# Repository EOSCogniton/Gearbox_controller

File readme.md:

# Gearbox controller

* Shield pour Arduino Uno
* Pour le shifter d'OPTIMUS v1.0

## Utilité :
* Convertis les signaux 12V du moteur en 5V pour l'arduino
* Convertis les signaux 5V de l'arduino en 12V pour le moteur
* Permet de se connecter avec des connecteurs molex KK à l'arduino
* Inclus un circuit de protection pour l'alimentation de l'arduino

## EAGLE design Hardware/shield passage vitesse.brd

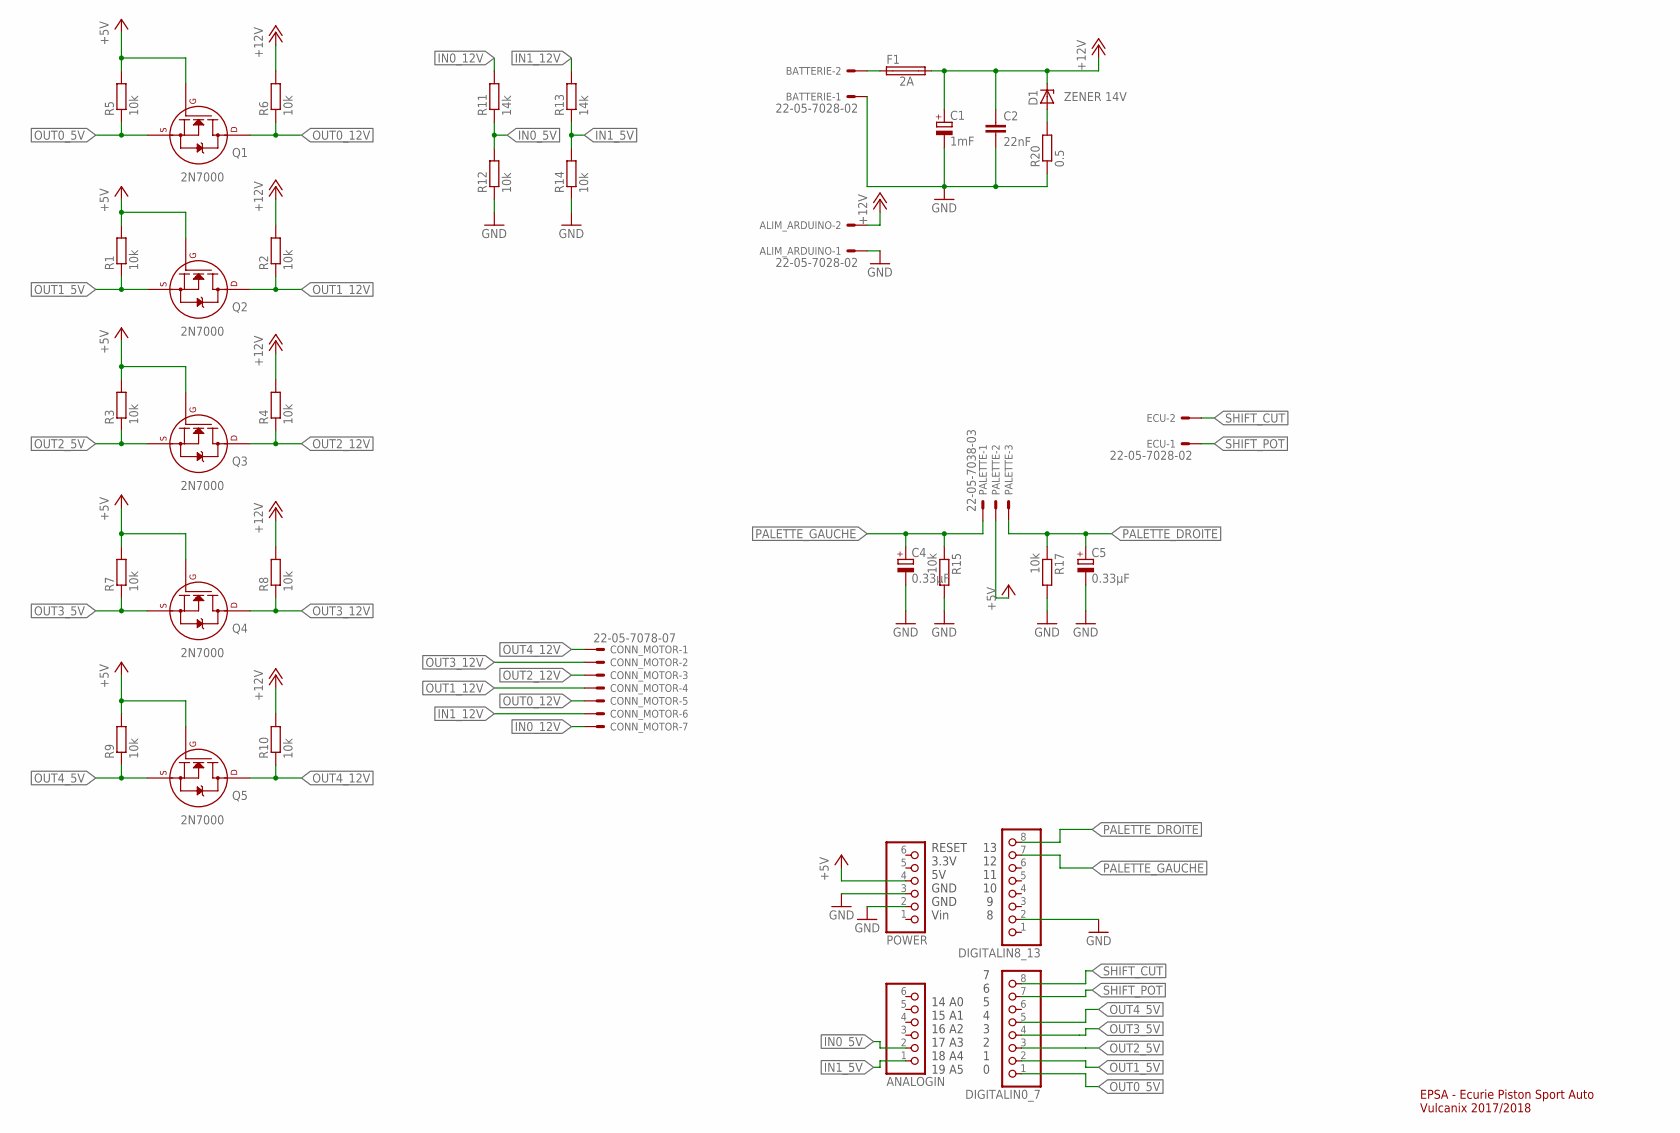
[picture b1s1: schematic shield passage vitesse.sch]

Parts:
ALIM_ARDUINO: 22-05-7028-02; 7395-02
ANALOGIN: PINHD-1X6CB; 1X06-CLEANBIG
BATTERIE: 22-05-7028-02; 7395-02
C1: 1mF; E7,5-16
C2: 22nF; C025-025X050
C4, C5: 0.33µF; E2,5-6E
CONN_MOTOR: 22-05-7078-07; 7395-07
D1: ZENER 14V; DO41Z10
DIGITALIN0_7, DIGITALIN8_13: PINHD-1X8CLEANBIG; 1X08-CLEANBIG
ECU: 22-05-7028-02; 7395-02
F1: 2A; SH25
PALETTE: 22-05-7038-03; 7395-03
POWER: PINHD-1X6CB; 1X06-CLEANBIG
Q1, Q2, Q3, Q4, Q5: 2N7000; TO-92
R1, R2, R3, R4, R5, R6, R7, R8, R9, R10, R12, R14, R15, R17: 10k; 0204/7
R11, R13: 14k; 0204/7
R20: 0.5; 0309/12

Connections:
+5V: PALETTE.2, POWER.4, Q1.2 (G), Q2.2 (G), Q3.2 (G), Q4.2 (G), Q5.2 (G), R1.2, R3.2, R5.2, R7.2, R9.2
+12V: ALIM_ARDUINO.2, C1.+, C2.1, D1.C, F1.2, R2.2, R4.2, R6.2, R8.2, R10.2
GND: ALIM_ARDUINO.1, BATTERIE.1, C1.-, C2.2, C4.-, C5.-, DIGITALIN8_13.2, POWER.2, POWER.3, R12.1, R14.1, R15.2, R17.2, R20.1
IN0_5V: ANALOGIN.2, R11.1, R12.2
IN0_12V: CONN_MOTOR.7, R11.2
IN1_5V: ANALOGIN.1, R13.1, R14.2
IN1_12V: CONN_MOTOR.6, R13.2
unnamed: BATTERIE.2, F1.1
unnamed: D1.A, R20.2
OUT0_5V: DIGITALIN0_7.1, Q1.1 (S), R5.1
OUT0_12V: CONN_MOTOR.5, Q1.3 (D), R6.1
OUT1_5V: DIGITALIN0_7.2, Q2.1 (S), R1.1
OUT1_12V: CONN_MOTOR.4, Q2.3 (D), R2.1
OUT2_5V: DIGITALIN0_7.3, Q3.1 (S), R3.1
OUT2_12V: CONN_MOTOR.3, Q3.3 (D), R4.1
OUT3_5V: DIGITALIN0_7.4, Q4.1 (S), R7.1
OUT3_12V: CONN_MOTOR.2, Q4.3 (D), R8.1
OUT4_5V: DIGITALIN0_7.5, Q5.1 (S), R9.1
OUT4_12V: CONN_MOTOR.1, Q5.3 (D), R10.1
PALETTE_DROITE: C5.+, DIGITALIN8_13.8, PALETTE.3, R17.1
PALETTE_GAUCHE: C4.+, DIGITALIN8_13.7, PALETTE.1, R15.1
SHIFT_CUT: DIGITALIN0_7.8, ECU.2
SHIFT_POT: DIGITALIN0_7.7, ECU.1

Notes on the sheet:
EPSA - Ecurie Piston Sport Auto Vulcanix 2017/2018
7 6 5 4 3 2 1 0
13 12 11 10 9 8
14 A0 15 A1 16 A2 17 A3 18 A4 19 A5
RESET 3.3V 5V GND GND Vin

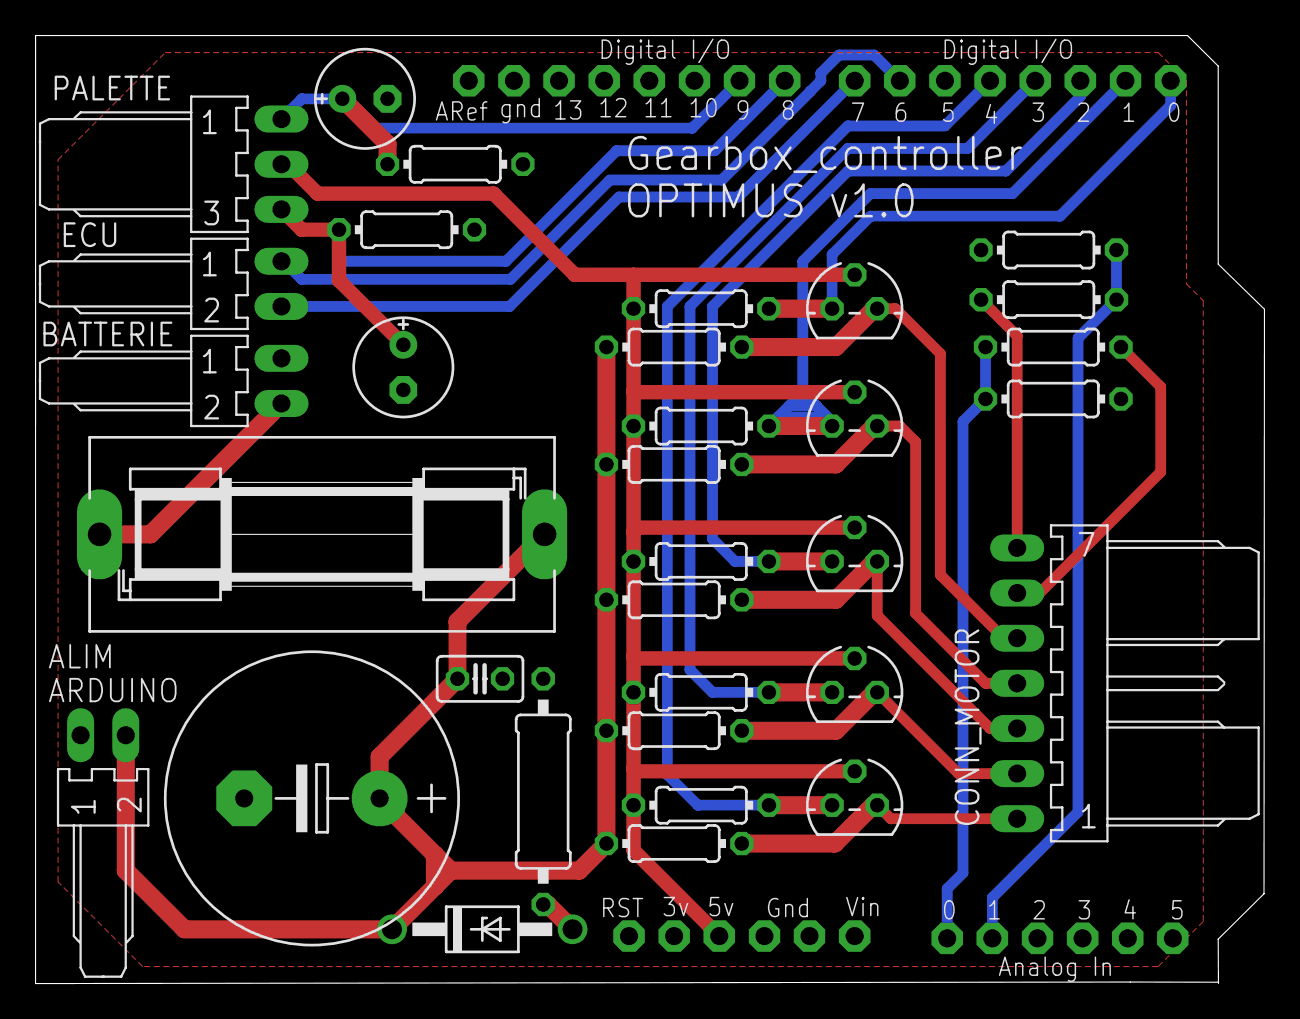
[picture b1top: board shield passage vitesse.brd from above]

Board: 2 copper layers, 69.2 x 53.4 mm, 37 parts (0 on the bottom side), 23 nets.

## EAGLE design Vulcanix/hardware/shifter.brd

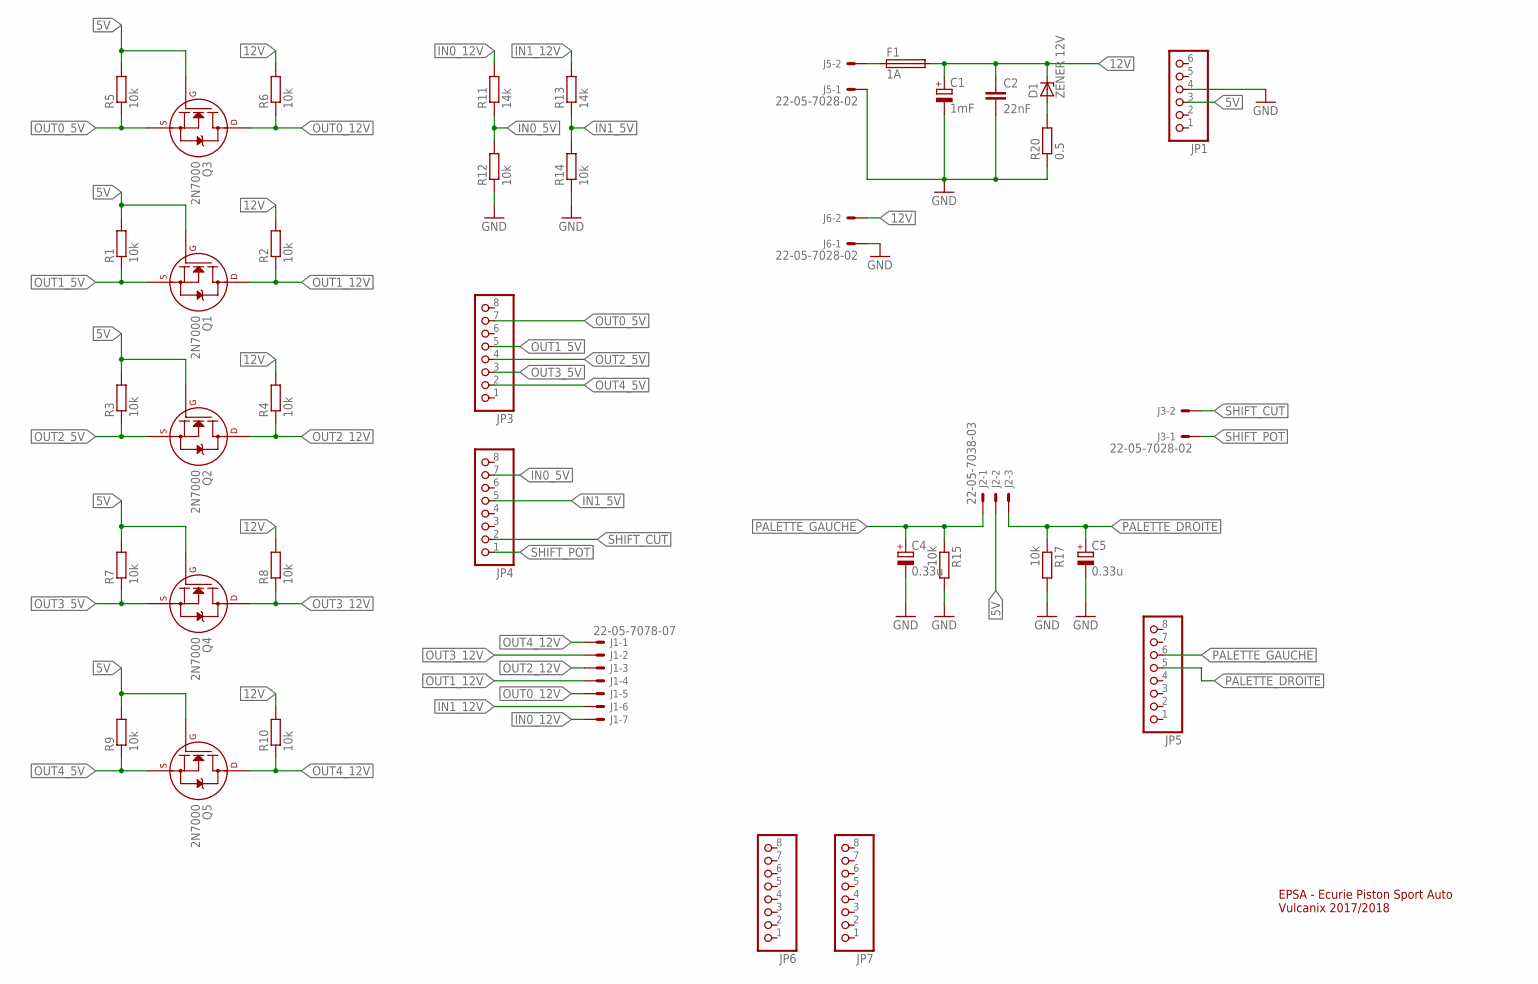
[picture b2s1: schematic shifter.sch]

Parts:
C1: 1mF; E7,5-16
C2: 22nF; C025-025X050
C4, C5: 0.33u; E2,5-6E
D1: ZENER 12V; DO41Z10
F1: 1A; SH25
J1: 22-05-7078-07; 7395-07
J2: 22-05-7038-03; 7395-03
J3, J5, J6: 22-05-7028-02; 7395-02
JP1: HEADER-1X6; 1X06_OVAL
JP3, JP4: HEADER-1X8; 1X08_OVAL
JP5, JP6, JP7: PINHD-1X8; 1X08
Q1, Q2, Q3, Q4, Q5: 2N7000; TO-92
R1, R2, R3, R4, R5, R6, R7, R8, R9, R10, R12, R14, R15, R17: 10k; 0204/7
R11, R13: 14k; 0204/7
R20: 0.5; 0309/12

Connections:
5V: J2.2, JP1.3, Q1.2 (G), Q2.2 (G), Q3.2 (G), Q4.2 (G), Q5.2 (G), R1.2, R3.2, R5.2, R7.2, R9.2
12V: C1.+, C2.1, D1.C, F1.2, J6.2, R2.2, R4.2, R6.2, R8.2, R10.2
GND: C1.-, C2.2, C4.-, C5.-, J5.1, J6.1, JP1.4, R12.1, R14.1, R15.2, R17.2, R20.1
IN0_5V: JP4.7, R11.1, R12.2
IN0_12V: J1.7, R11.2
IN1_5V: JP4.5, R13.1, R14.2
IN1_12V: J1.6, R13.2
unnamed: F1.1, J5.2
unnamed: D1.A, R20.2
OUT0_5V: JP3.7, Q3.1 (S), R5.1
OUT0_12V: J1.5, Q3.3 (D), R6.1
OUT1_5V: JP3.5, Q1.1 (S), R1.1
OUT1_12V: J1.4, Q1.3 (D), R2.1
OUT2_5V: JP3.4, Q2.1 (S), R3.1
OUT2_12V: J1.3, Q2.3 (D), R4.1
OUT3_5V: JP3.3, Q4.1 (S), R7.1
OUT3_12V: J1.2, Q4.3 (D), R8.1
OUT4_5V: JP3.2, Q5.1 (S), R9.1
OUT4_12V: J1.1, Q5.3 (D), R10.1
PALETTE_DROITE: C5.+, J2.3, JP5.5, R17.1
PALETTE_GAUCHE: C4.+, J2.1, JP5.6, R15.1
SHIFT_CUT: J3.2, JP4.2
SHIFT_POT: J3.1, JP4.1

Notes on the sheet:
EPSA - Ecurie Piston Sport Auto Vulcanix 2017/2018

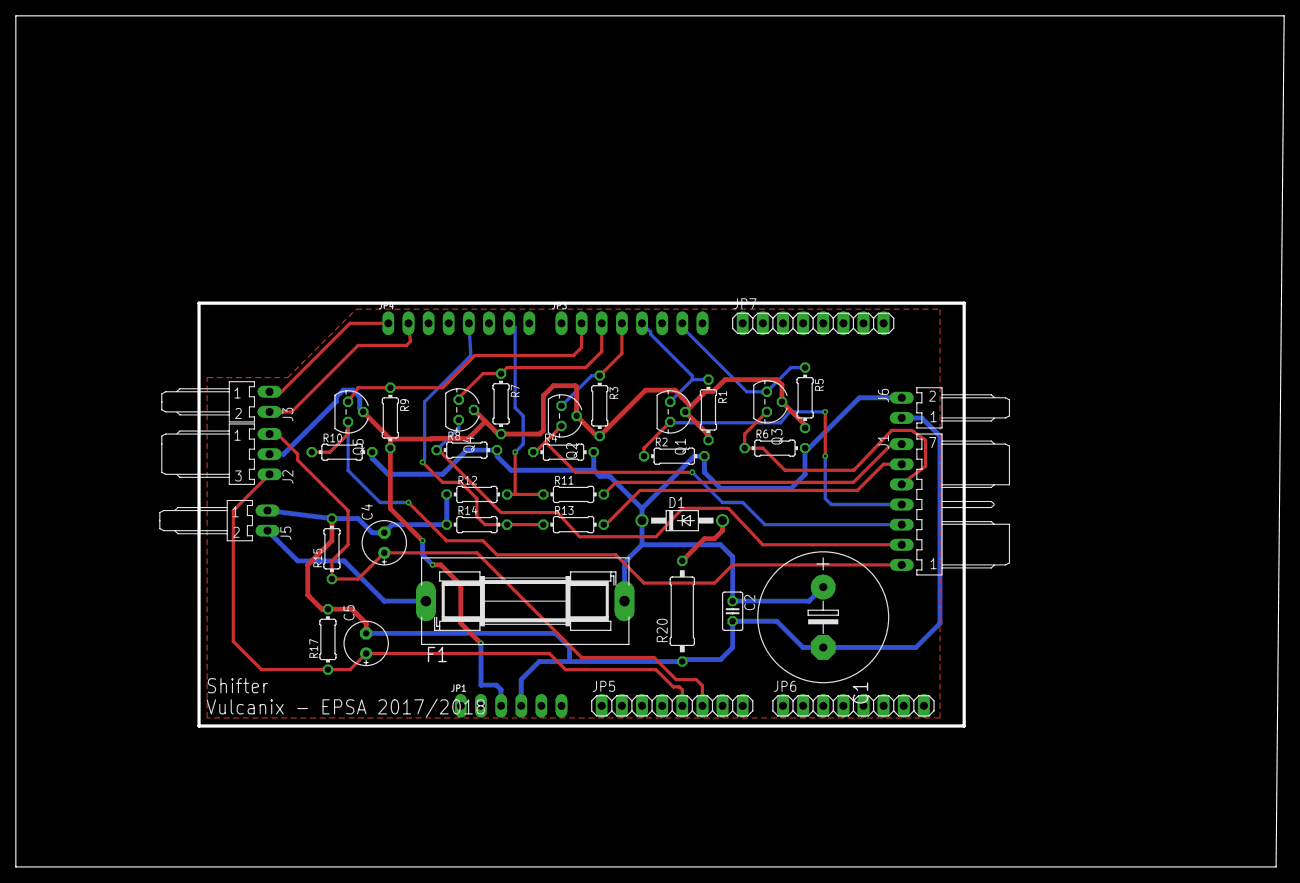
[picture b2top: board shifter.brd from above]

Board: 2 copper layers, 160.0 x 107.4 mm, 39 parts (0 on the bottom side), 23 nets.

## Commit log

2018-12-04 Create README.txt
    dftgyhujikol
2018-12-07 depot du travail actuel
2018-12-16 Déplacement des connecteurs à l'intérieur de la carte
2018-12-18 Passage de la Zener à 15V et ajout des convention +5 V et +12V
2018-12-18 Suppression dossier Vulcanix (dèjà disponible sur un autre dépôt)
2018-12-18 Passage de la Zener à 14V
2018-12-22 Création de fichiers d'usinage
2019-01-08 zip usinage
2019-01-08 Mise en qualité
2019-01-13 Ajout readme
2019-01-19 Ajout du gitignore
2019-01-19 Passage à la version de dev suivante
2019-03-05 Finalisation code arduino passage de vitesse
2019-04-06 code
2019-04-06 Correction pb de double fichier
2019-04-06 Correction pin
2019-04-17 MAJ du code
2019-04-22 Ajout fiche carte
2019-05-03 maj main code et ajout code avec un mode auto
2019-05-22 maj code suite à des problème instabilité du can lors de l'init
2019-06-10 Programme motored
2019-08-03 modif passage auto pas au point en italie
2019-10-23 Ajout code de la carte d'optimus dans Vulcanix (pas de CAN)

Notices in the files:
parts and their libraries:
microbuilder: This work is placed in the public domain, and may be freely used for commercial and non-commercial work with the following conditions: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
